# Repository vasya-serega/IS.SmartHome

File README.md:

# IS.SmartHome
Smart home solution

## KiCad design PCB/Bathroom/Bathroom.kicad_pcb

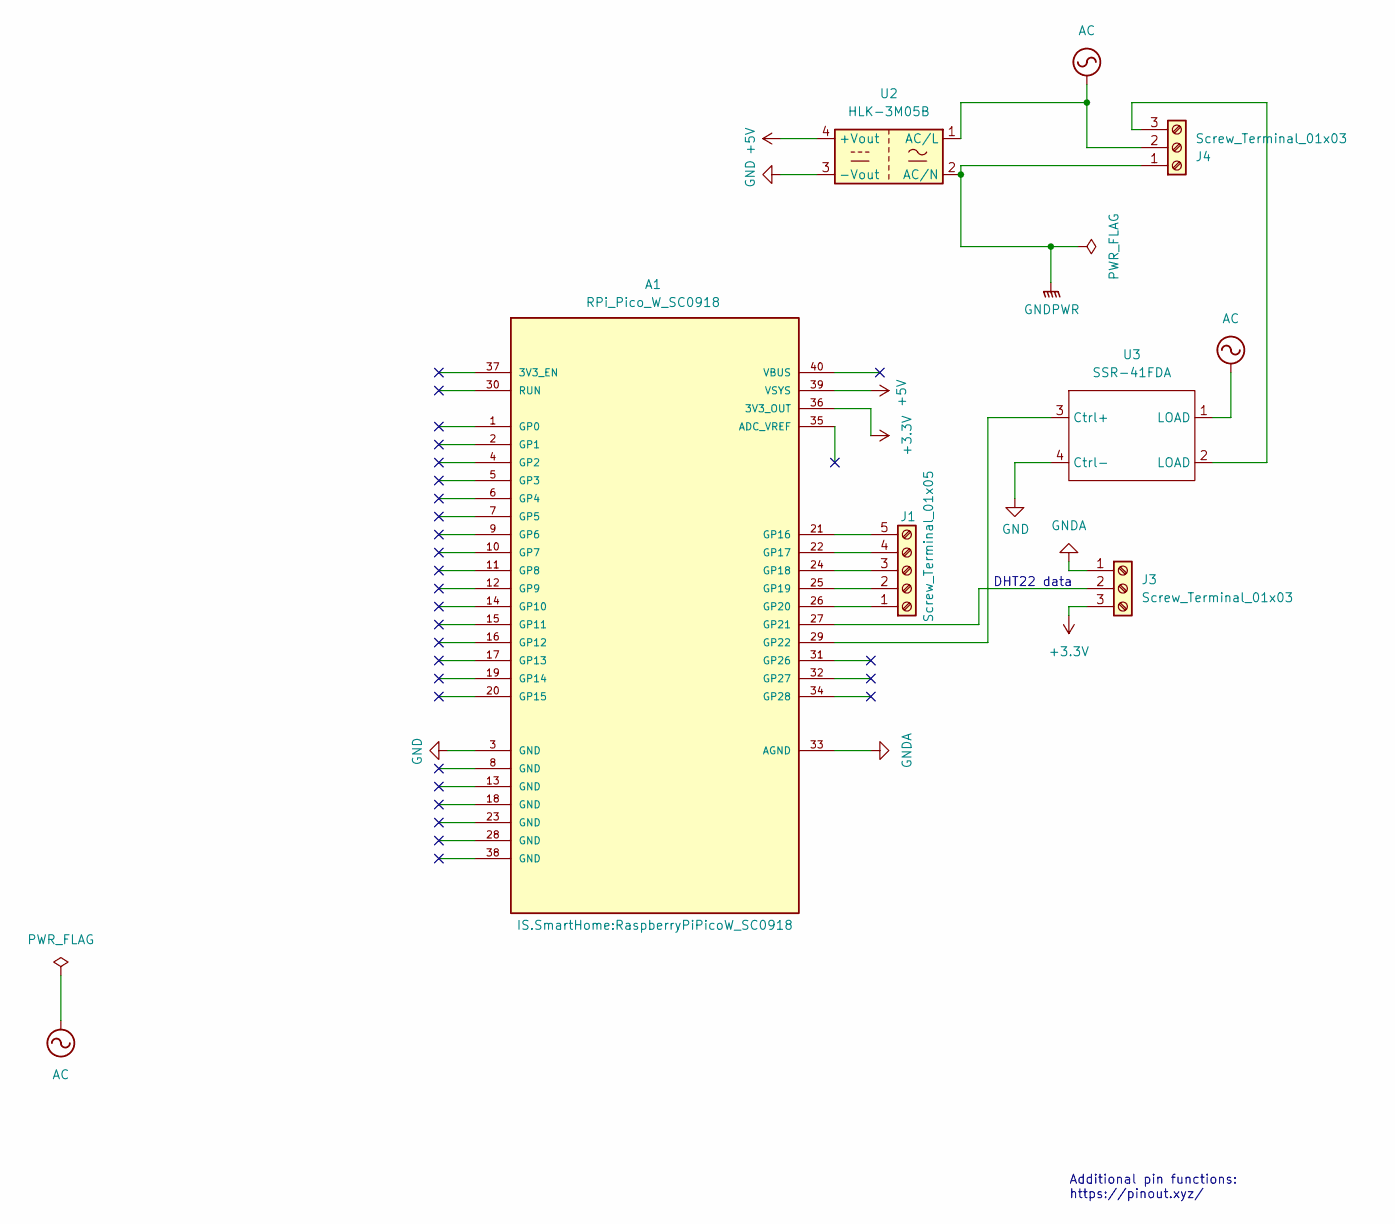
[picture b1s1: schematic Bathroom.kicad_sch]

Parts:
A1: RPi_Pico_W_SC0918; RaspberryPiPicoW_SC0918; PARTREV 1.6
J1: Screw_Terminal_01x05; TerminalBlock_Phoenix_MKDS-1-5-3.81_1x05_P3.81mm_Horizontal
J3, J4: Screw_Terminal_01x03; TerminalBlock_Phoenix_MKDS-1,5-3-5.08_1x03_P5.08mm_Horizont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
U2: HLK-3M05B; Converter_ACDC_Hi-Link_HLK-PMxx
U3: SSR-41FDA

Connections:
+3.3V: A1.36 (3V3_OUT), J3.3
+5V: A1.39 (VSYS), U2.4 (+Vout)
AC: J4.2, U2.1 (AC/L), U3.1 (LOAD)
GND: A1.3 (GND), U2.3 (-Vout), U3.4 (Ctrl-)
GNDA: A1.33 (AGND), J3.1
GNDPWR: J4.1, U2.2 (AC/N)
unnamed: A1.21 (GP16), J1.5
unnamed: A1.22 (GP17), J1.4
unnamed: A1.24 (GP18), J1.3
unnamed: A1.25 (GP19), J1.2
unnamed: A1.26 (GP20), J1.1
unnamed: A1.27 (GP21), J3.2
unnamed: A1.29 (GP22), U3.3 (Ctrl+)
unnamed: J4.3, U3.2 (LOAD)

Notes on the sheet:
Additional pin functions: https://pinout.xyz/
DHT22 data

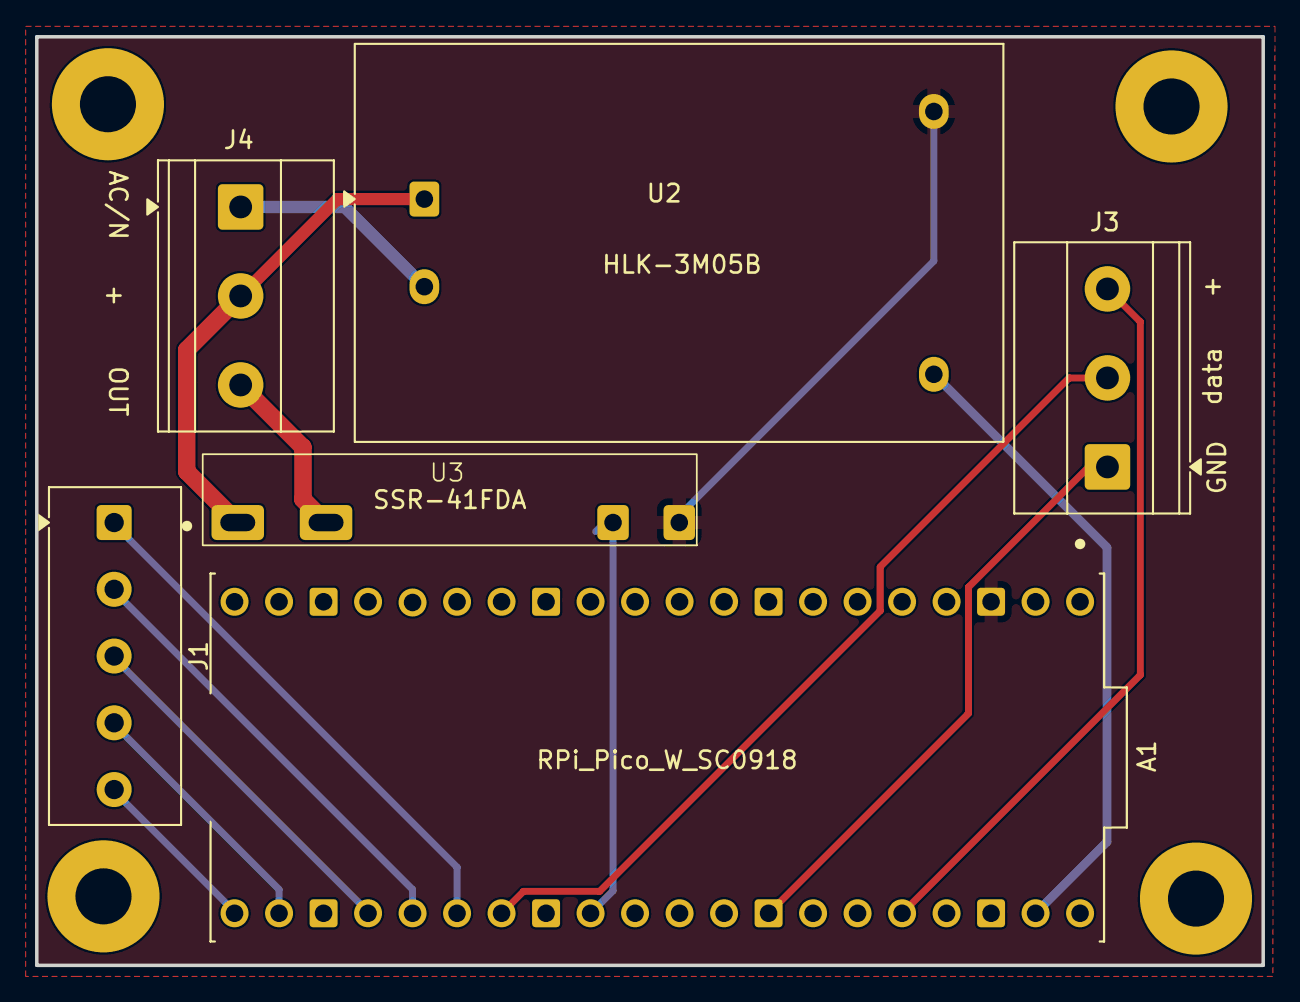
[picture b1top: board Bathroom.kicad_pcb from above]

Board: 2 copper layers, 70.0 x 53.0 mm, 6 parts (0 on the bottom side), 14 nets.
